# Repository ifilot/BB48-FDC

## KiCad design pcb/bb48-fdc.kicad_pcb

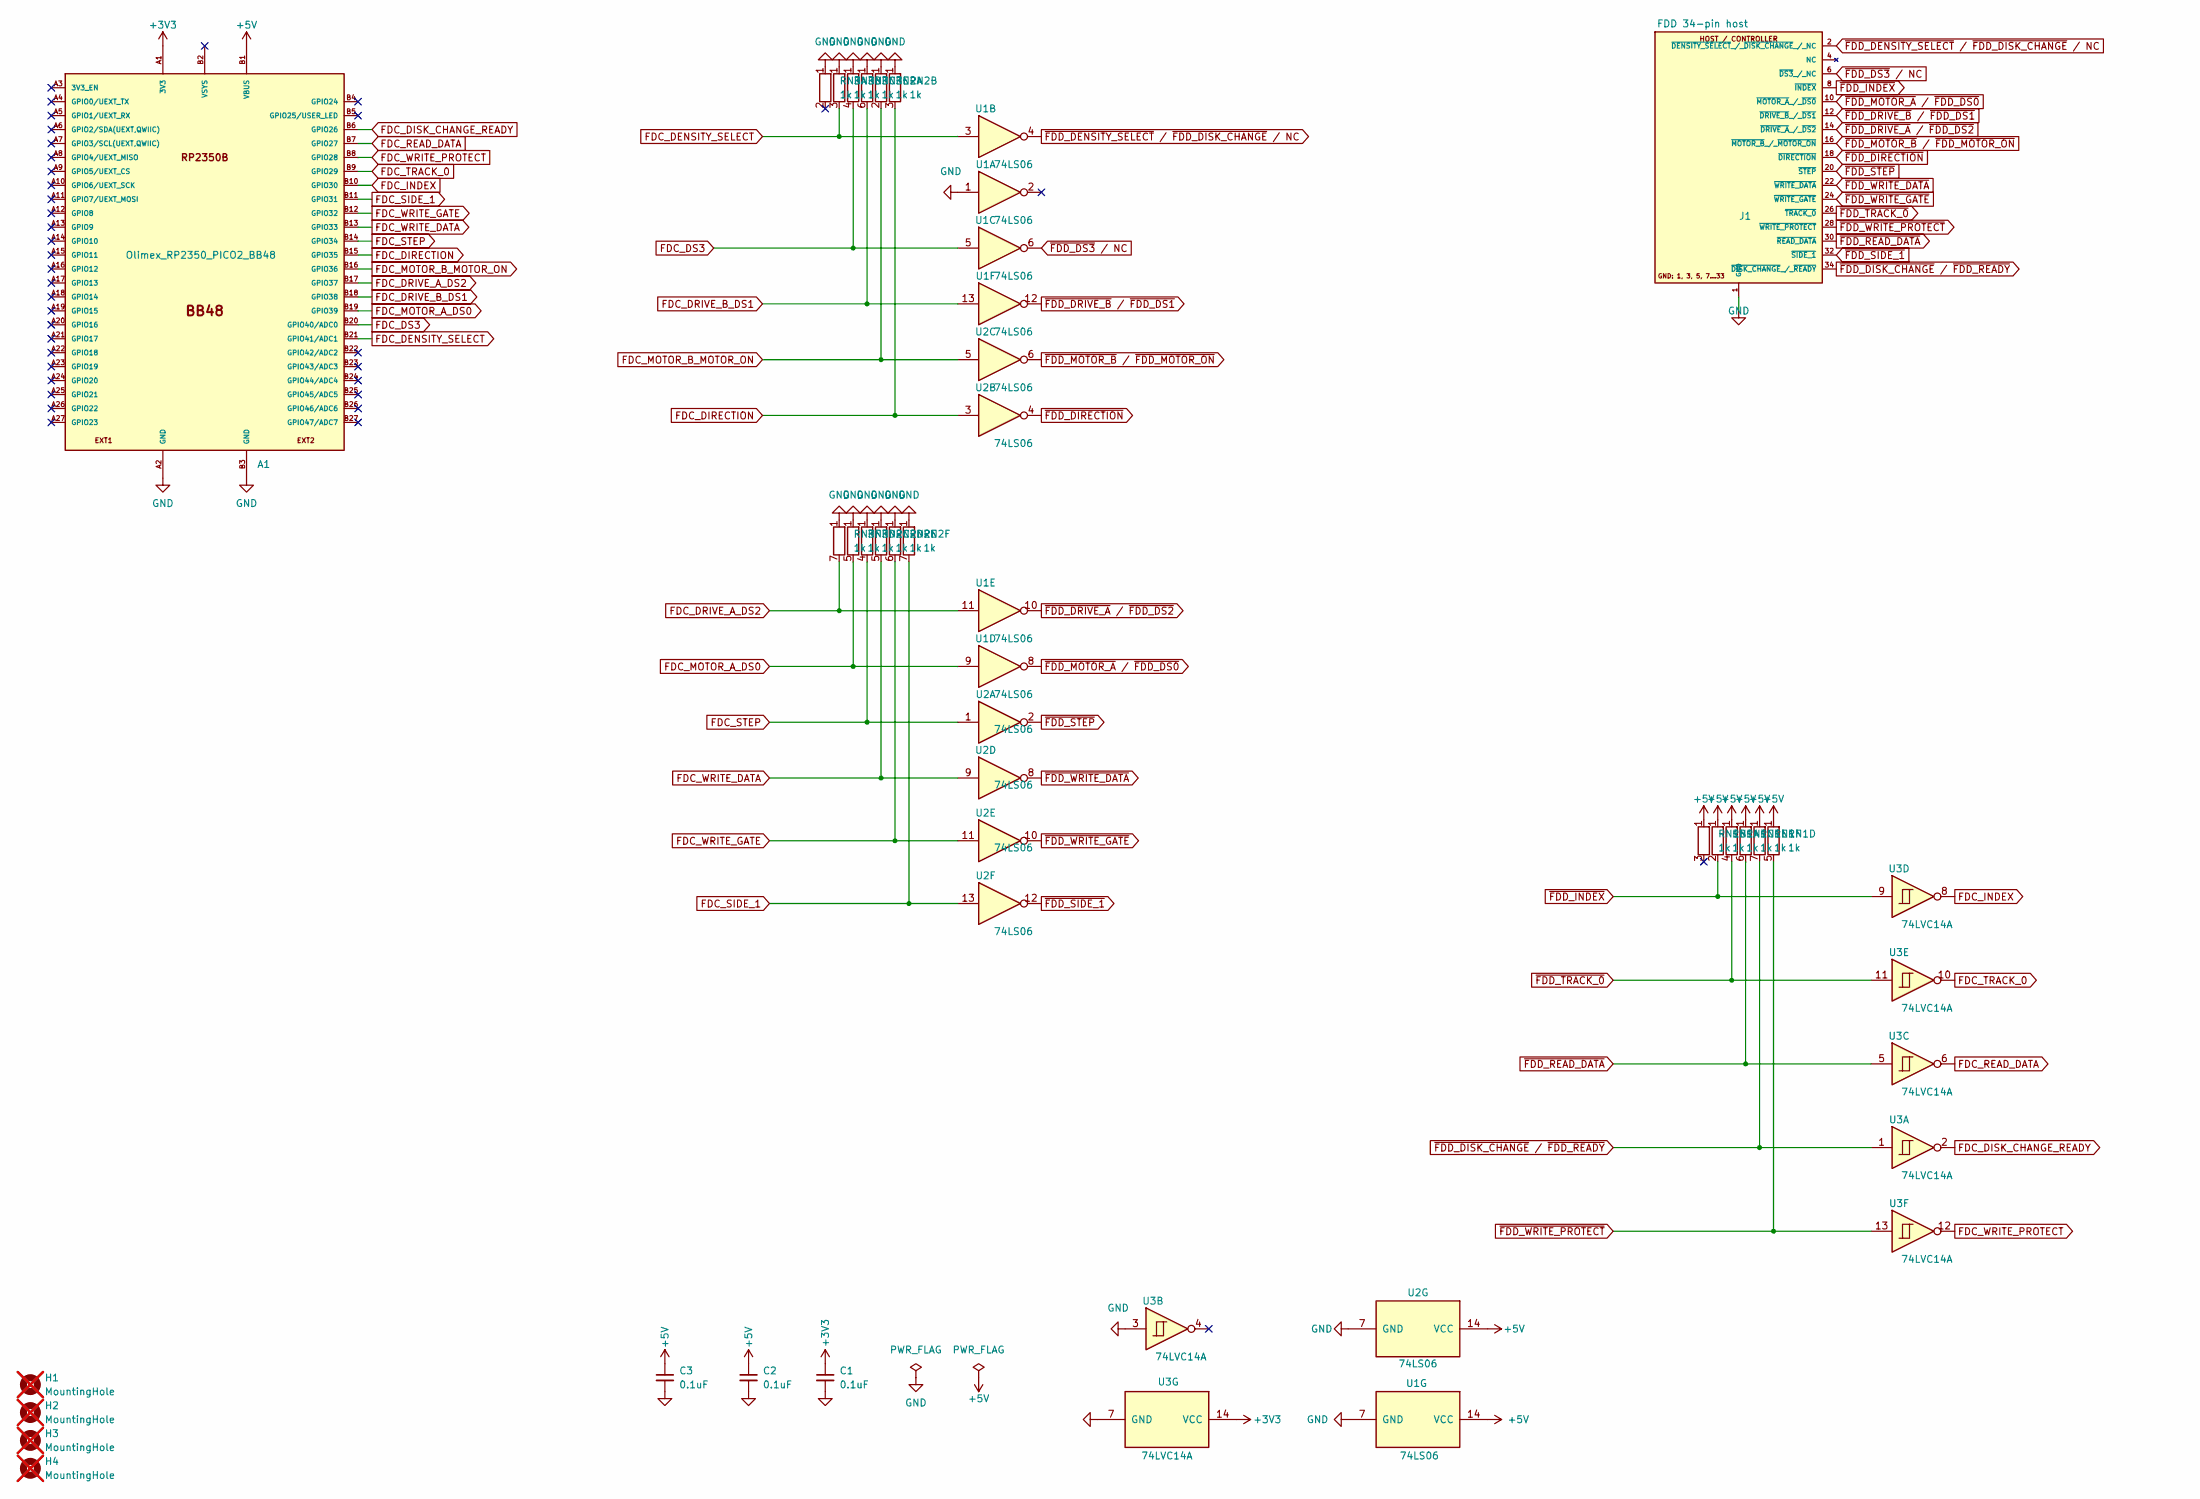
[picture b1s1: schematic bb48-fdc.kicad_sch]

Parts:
A1: Olimex_RP2350_PICO2_BB48
C1, C2, C3: 0.1uF; C_0805_2012Metric_Pad1.18x1.45mm_HandSolder
H1, H2, H3, H4: MountingHole; not fitted
J1: FDD 34-pin host; IDC-Header_2x17_P2.54mm_Vertical
RN1, RN2, RN3: 1k; R_Array_SIP7
U1, U2: 74LS06; SOIC-14_3.9x8.7mm_P1.27mm
U3: 74LVC14A; SOIC-14_3.9x8.7mm_P1.27mm

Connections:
+3V3: A1.A1 (3V3), C1.1, U3.14 (VCC)
+5V: A1.B1 (VBUS), C2.1, C3.1, RN1.1 (R1), U1.14 (VCC), U2.14 (VCC)
FDC_DENSITY_SELECT: A1.B21 (GPIO41/ADC1), RN3.3 (R2.2), U1.3
FDC_DIRECTION: A1.B15 (GPIO35), RN2.3 (R2.2), U2.3
FDC_DISK_CHANGE_READY: A1.B6 (GPIO26), U3.2
FDC_DRIVE_A_DS2: A1.B17 (GPIO37), RN3.7 (R6.2), U1.11
FDC_DRIVE_B_DS1: A1.B18 (GPIO38), RN3.6 (R5.2), U1.13
FDC_DS3: A1.B20 (GPIO40/ADC0), RN3.4 (R3.2), U1.5
FDC_INDEX: A1.B10 (GPIO30), U3.8
FDC_MOTOR_A_DS0: A1.B19 (GPIO39), RN3.5 (R4.2), U1.9
FDC_MOTOR_B_MOTOR_ON: A1.B16 (GPIO36), RN2.2 (R1.2), U2.5
FDC_READ_DATA: A1.B7 (GPIO27), U3.6
FDC_SIDE_1: A1.B11 (GPIO31), RN2.7 (R6.2), U2.13
FDC_STEP: A1.B14 (GPIO34), RN2.4 (R3.2), U2.1
FDC_TRACK_0: A1.B9 (GPIO29), U3.10
FDC_WRITE_DATA: A1.B13 (GPIO33), RN2.5 (R4.2), U2.9
FDC_WRITE_GATE: A1.B12 (GPIO32), RN2.6 (R5.2), U2.11
FDC_WRITE_PROTECT: A1.B8 (GPIO28), U3.12
GND: A1.A2 (GND), A1.B3 (GND), C1.2, C2.2, C3.2, J1.1 (GND), J1.3 (GND), J1.5 (GND), J1.7 (GND), J1.9 (GND), J1.11 (GND), J1.13 (GND), J1.15 (GND), J1.17 (GND), J1.19 (GND), J1.21 (GND), J1.23 (GND), J1.25 (GND), J1.27 (GND), J1.29 (GND), J1.31 (GND), J1.33 (GND), RN2.1 (R1), RN3.1 (R1), U1.1, U1.7 (GND), U2.7 (GND), U3.3, U3.7 (GND)
~FDD_DENSITY_SELECT / ~FDD_DISK_CHANGE / NC: J1.2 (~DENSITY_SELECT_/_~DISK_CHANGE_/_NC), U1.4
~FDD_DIRECTION: J1.18 (~DIRECTION), U2.4
~FDD_DISK_CHANGE / ~FDD_READY: J1.34 (~DISK_CHANGE_/_~READY), RN1.7 (R6.2), U3.1
~FDD_DRIVE_A / ~FDD_DS2: J1.14 (~DRIVE_A_/_~DS2), U1.10
~FDD_DRIVE_B / ~FDD_DS1: J1.12 (~DRIVE_B_/_~DS1), U1.12
~FDD_DS3 / NC: J1.6 (~DS3_/_NC), U1.6
~FDD_INDEX: J1.8 (~INDEX), RN1.2 (R1.2), U3.9
~FDD_MOTOR_A / ~FDD_DS0: J1.10 (~MOTOR_A_/_~DS0), U1.8
~FDD_MOTOR_B / ~FDD_MOTOR_ON: J1.16 (~MOTOR_B_/_~MOTOR_ON), U2.6
~FDD_READ_DATA: J1.30 (~READ_DATA), RN1.6 (R5.2), U3.5
~FDD_SIDE_1: J1.32 (~SIDE_1), U2.12
~FDD_STEP: J1.20 (~STEP), U2.2
~FDD_TRACK_0: J1.26 (~TRACK_0), RN1.4 (R3.2), U3.11
~FDD_WRITE_DATA: J1.22 (~WRITE_DATA), U2.8
~FDD_WRITE_GATE: J1.24 (~WRITE_GATE), U2.10
~FDD_WRITE_PROTECT: J1.28 (~WRITE_PROTECT), RN1.5 (R4.2), U3.13

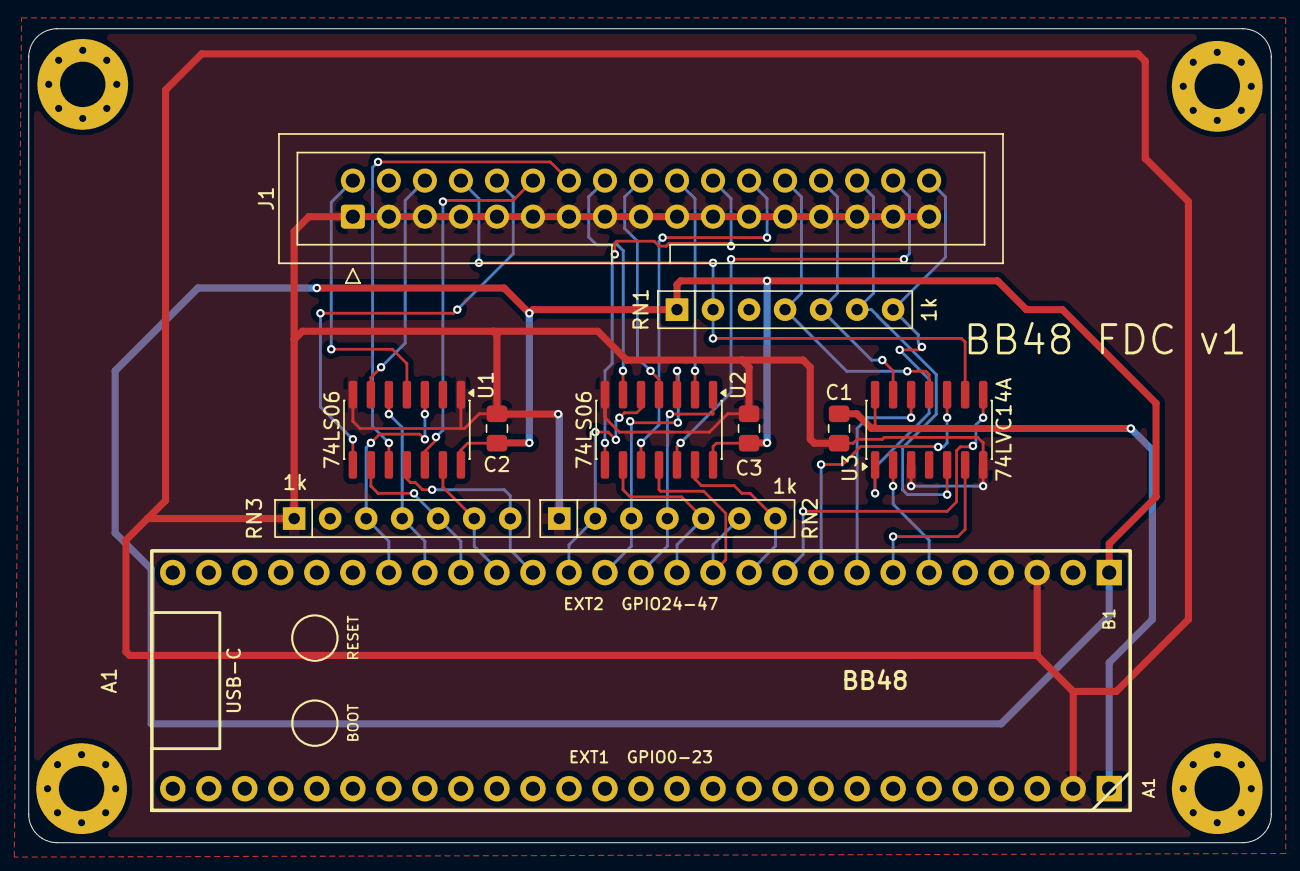
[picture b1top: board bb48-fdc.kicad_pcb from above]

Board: 2 copper layers, 87.6 x 57.4 mm, 15 parts (0 on the bottom side), 35 nets.
